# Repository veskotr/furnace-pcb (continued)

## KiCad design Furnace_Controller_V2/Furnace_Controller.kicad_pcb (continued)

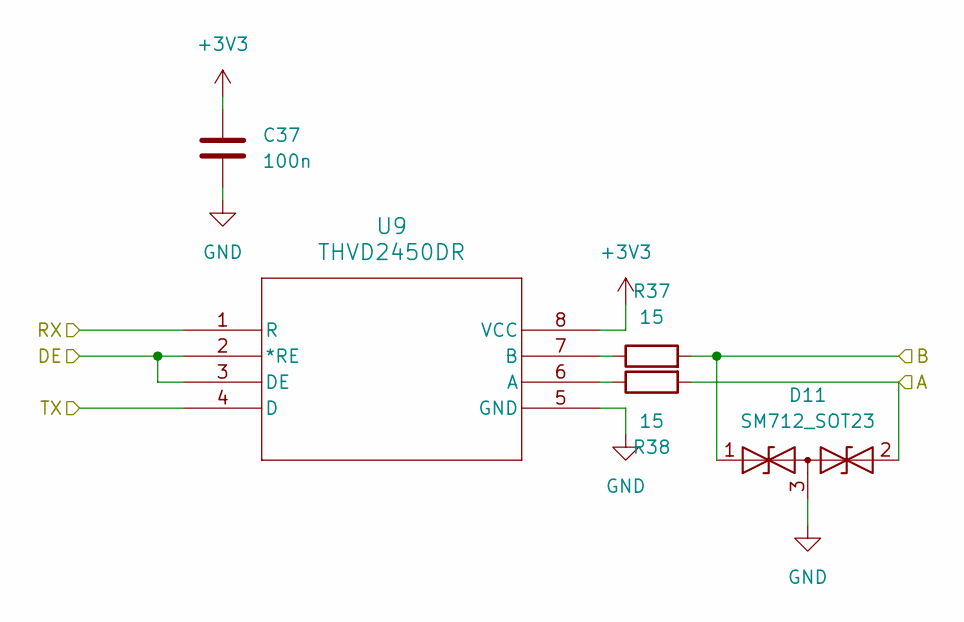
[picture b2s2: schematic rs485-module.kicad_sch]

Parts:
C37: 100n; C_0603_1608Metric
D11: SM712_SOT23; SOT-23
R37, R38: 15; R_0603_1608Metric
U9: THVD2450DR; SOIC-8_3.9x4.9mm_P1.27mm

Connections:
+3V3: C37.1, U9.8 (VCC); also elsewhere on the board
/RS_485_DIR: U9.2 (*RE), U9.3 (DE); also elsewhere on the board
/UART2_RX: U9.1 (R); also elsewhere on the board
/UART2_TX: U9.4 (D); also elsewhere on the board
/rs485-module/A: D11.2 (A2), R38.2; also elsewhere on the board
/rs485-module/B: D11.1 (A1), R37.2; also elsewhere on the board
GND: C37.2, D11.3 (common), U9.5 (GND); also elsewhere on the board
unnamed: R38.1, U9.6 (A)
unnamed: R37.1, U9.7 (B)

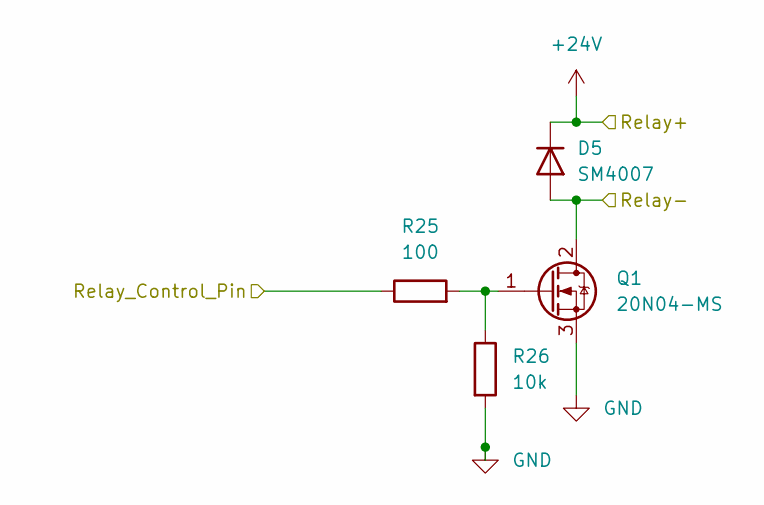
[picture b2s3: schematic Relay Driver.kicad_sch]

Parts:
D5: SM4007; D_SOD-123
Q1: 20N04-MS; Q_SOT-89
R25: 100; R_0603_1608Metric
R26: 10k; R_0603_1608Metric

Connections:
+24V: D5.1 (K); also elsewhere on the board
/Heater_Relay_Pin: R25.1; also elsewhere on the board
/Relay Driver/Relay-: D5.2 (A), Q1.2 (D); also elsewhere on the board
GND: Q1.3 (S), R26.2; also elsewhere on the board
unnamed: Q1.1 (G), R25.2, R26.1

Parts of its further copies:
D6, D7, D8: SM4007; D_SOD-123
Q2, Q3, Q4: 20N04-MS; Q_SOT-89
R27, R29, R31: 100; R_0603_1608Metric
R28, R30, R32: 10k; R_0603_1608Metric

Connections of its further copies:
+24V: D6.1 (K), D7.1 (K), D8.1 (K); also elsewhere on the board
/Aux2_Relay_Pin: R31.1; also elsewhere on the board
/Aux_Relay_Pin: R29.1; also elsewhere on the board
/Fan_Relay_Pin: R27.1; also elsewhere on the board
/Relay Driver1/Relay-: D6.2 (A), Q2.2 (D); also elsewhere on the board
/Relay Driver2/Relay-: D7.2 (A), Q3.2 (D); also elsewhere on the board
/Relay Driver3/Relay-: D8.2 (A), Q4.2 (D); also elsewhere on the board
GND: Q2.3 (S), Q3.3 (S), Q4.3 (S), R28.2, R30.2, R32.2; also elsewhere on the board
unnamed: Q2.1 (G), R27.2, R28.1
unnamed: Q3.1 (G), R29.2, R30.1
unnamed: Q4.1 (G), R31.2, R32.1

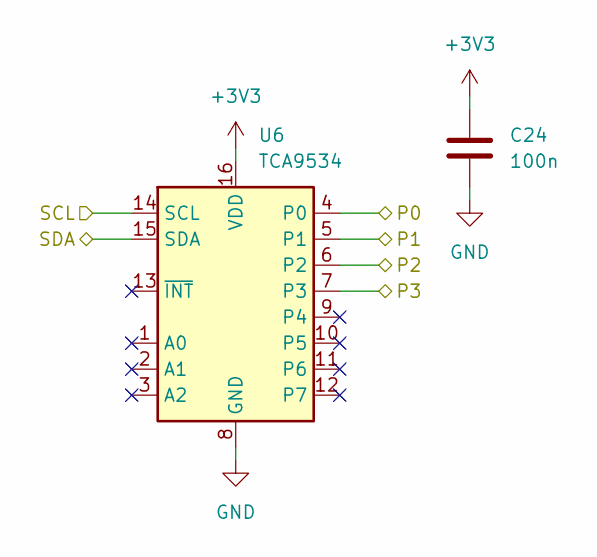
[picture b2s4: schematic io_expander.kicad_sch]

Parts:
C24: 100n; C_0603_1608Metric
U6: TCA9534; TSSOP-16_4.4x5mm_P0.65mm

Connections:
+3V3: C24.1, U6.16 (VDD); also elsewhere on the board
/Aux2_Relay_Pin: U6.7 (P3); also elsewhere on the board
/Aux_Relay_Pin: U6.6 (P2); also elsewhere on the board
/Fan_Relay_Pin: U6.5 (P1); also elsewhere on the board
/Heater_Relay_Pin: U6.4 (P0); also elsewhere on the board
/SCL: U6.14 (SCL); also elsewhere on the board
/SDA: U6.15 (SDA); also elsewhere on the board
GND: C24.2, U6.8 (GND); also elsewhere on the board

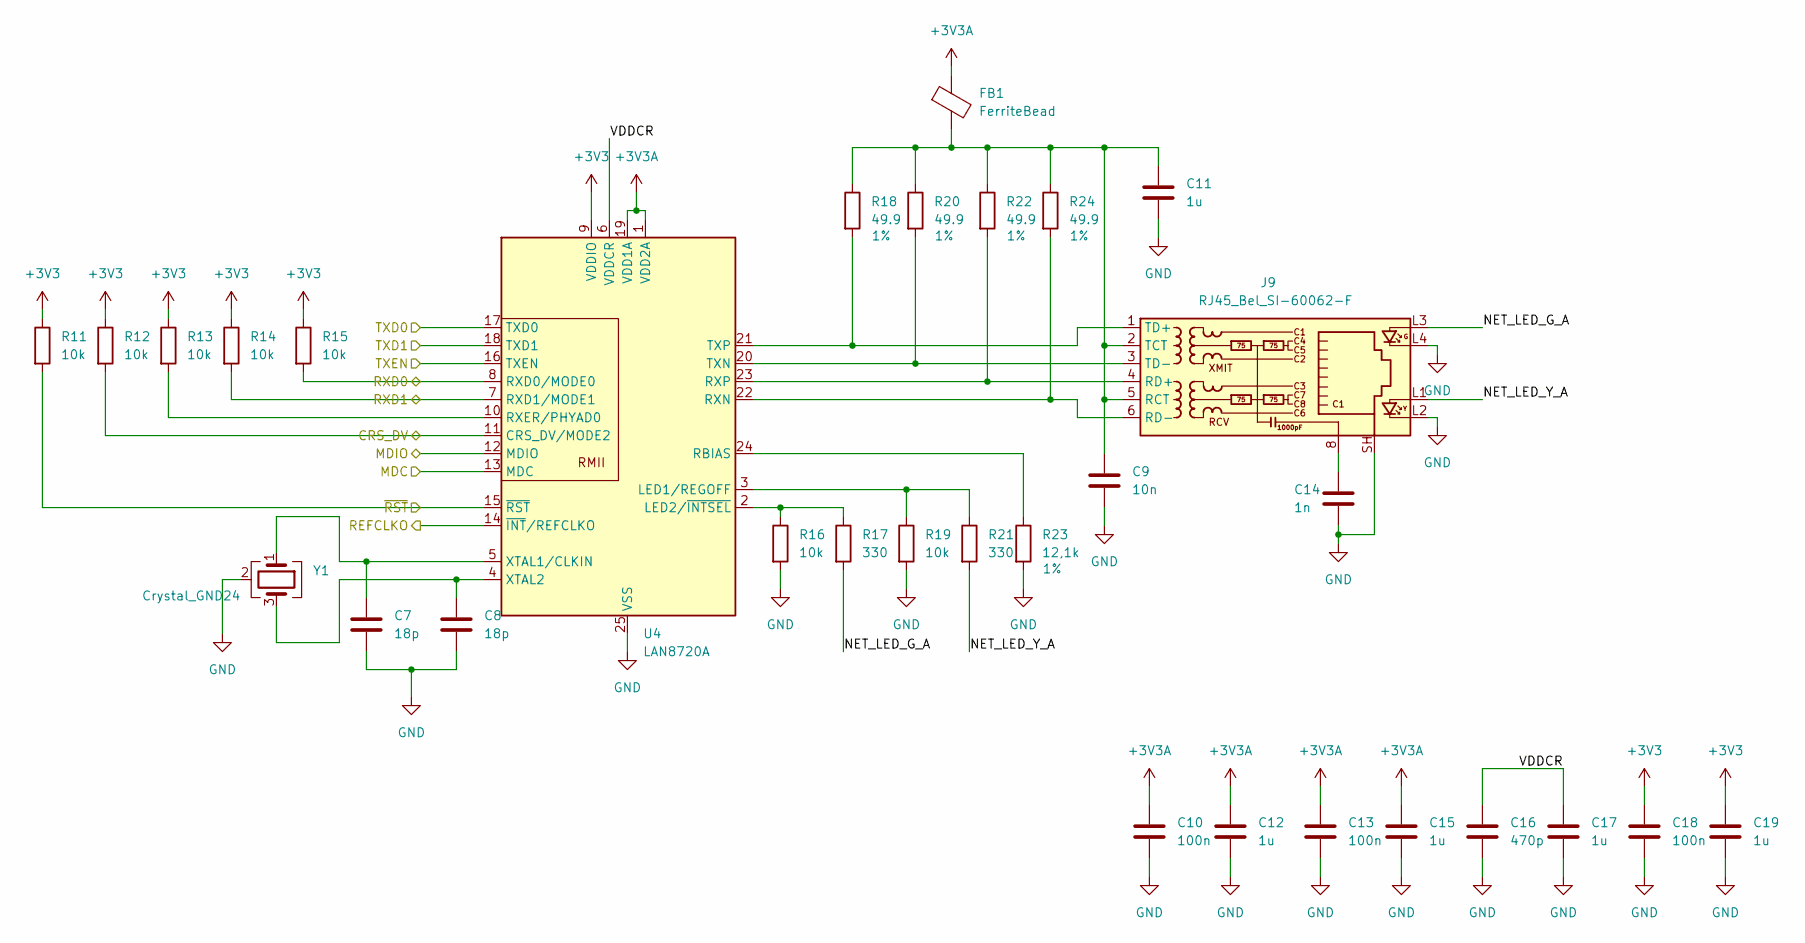
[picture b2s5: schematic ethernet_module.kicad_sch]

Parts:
C7, C8: 18p; C_0603_1608Metric
C9: 10n; C_0603_1608Metric
C10, C13, C18: 100n; C_0603_1608Metric
C11, C12, C15, C17, C19: 1u; C_0603_1608Metric
C14: 1n; C_1808_4520Metric
C16: 470p; C_0603_1608Metric
FB1: FerriteBead; L_0603_1608Metric
J9: RJ45_Bel_SI-60062-F
R11, R12, R13, R14, R15, R16, R19: 10k; R_0603_1608Metric
R17, R21: 330; R_0603_1608Metric
R18, R20, R22, R24: 49.9; R_0603_1608Metric
R23: 12,1k; R_0603_1608Metric
U4: LAN8720A; VQFN-24-1EP_4x4mm_P0.5mm_EP2.5x2.5mm_ThermalVias
Y1: Crystal_GND24; Crystal_SMD_3225-4Pin_3.2x2.5mm

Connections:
+3V3: C18.1, C19.1, R11.1, R12.1, R13.1, R14.1, R15.1, U4.9 (VDDIO); also elsewhere on the board
+3V3A: C10.1, C12.1, C13.1, C15.1, FB1.1, U4.1 (VDD2A), U4.19 (VDD1A); also elsewhere on the board
/CRS_DV: R12.2, U4.11 (CRS_DV/MODE2); also elsewhere on the board
/Ethernet Module/NET_LED_G_A: J9.L3, R17.2
/Ethernet Module/NET_LED_Y_A: J9.L1, R21.2
/Ethernet Module/VDDCR: C16.1, C17.1, U4.6 (VDDCR)
/MDC: U4.13 (MDC); also elsewhere on the board
/MDIO: U4.12 (MDIO); also elsewhere on the board
/REFCLKO: U4.14 (~INT/REFCLKO); also elsewhere on the board
/RXD0: R15.2, U4.8 (RXD0/MODE0); also elsewhere on the board
/RXD1: R14.2, U4.7 (RXD1/MODE1); also elsewhere on the board
/TXD0: U4.17 (TXD0); also elsewhere on the board
/TXD1: U4.18 (TXD1); also elsewhere on the board
/TXEN: U4.16 (TXEN); also elsewhere on the board
/~RST: R11.2, U4.15 (~RST); also elsewhere on the board
GND: C7.1, C8.2, C9.2, C10.2, C11.2, C12.2, C13.2, C14.2, C15.2, C16.2, C17.2, C18.2, C19.2, J9.L2, J9.L4, J9.SH, R16.2, R19.2, R23.2, U4.25 (VSS), Y1.2 (G), Y1.4 (G); also elsewhere on the board
unnamed: C14.1, J9.8
unnamed: C9.1, C11.1, FB1.2, J9.2 (TCT), J9.5 (RCT), R18.1, R20.1, R22.1, R24.1
unnamed: J9.4 (RD+), R22.2, U4.23 (RXP)
unnamed: J9.6 (RD-), R24.2, U4.22 (RXN)
unnamed: J9.1 (TD+), R18.2, U4.21 (TXP)
unnamed: J9.3 (TD-), R20.2, U4.20 (TXN)
unnamed: R19.1, R21.1, U4.3 (LED1/REGOFF)
unnamed: R16.1, R17.1, U4.2 (LED2/~INTSEL)
unnamed: R23.1, U4.24 (RBIAS)
unnamed: R13.2, U4.10 (RXER/PHYAD0)
unnamed: C7.2, U4.5 (XTAL1/CLKIN), Y1.1
unnamed: C8.1, U4.4 (XTAL2), Y1.3

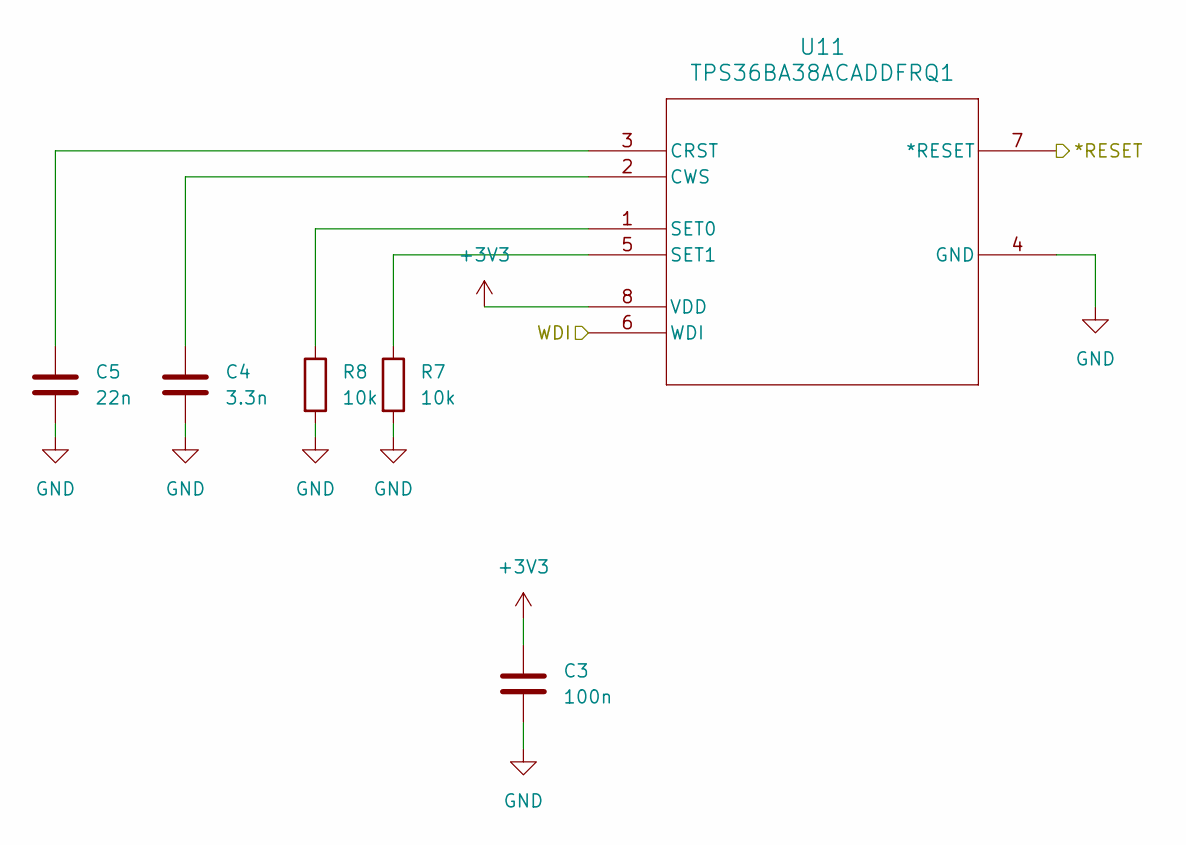
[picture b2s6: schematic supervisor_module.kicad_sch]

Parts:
C3: 100n; C_0603_1608Metric
C4: 3.3n; C_0603_1608Metric
C5: 22n; C_0603_1608Metric
R7, R8: 10k; R_0603_1608Metric
U11: TPS36BA38ACADDFRQ1; SOT-23-THIN-8_DDF_TEX

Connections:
+3V3: C3.1, U11.8 (VDD); also elsewhere on the board
/*RESET: U11.7 (*RESET); also elsewhere on the board
/WDI: U11.6 (WDI); also elsewhere on the board
GND: C3.2, C4.2, C5.2, R7.2, R8.2, U11.4 (GND); also elsewhere on the board
unnamed: C5.1, U11.3 (CRST)
unnamed: C4.1, U11.2 (CWS)
unnamed: R8.1, U11.1 (SET0)
unnamed: R7.1, U11.5 (SET1)

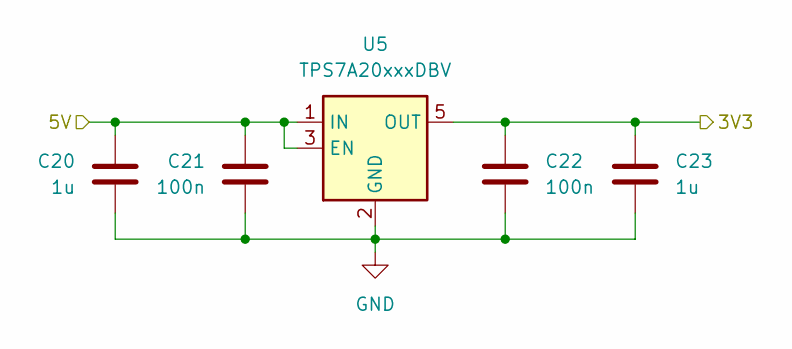
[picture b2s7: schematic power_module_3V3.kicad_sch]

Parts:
C20, C23: 1u; C_0603_1608Metric
C21, C22: 100n; C_0603_1608Metric
U5: TPS7A20xxxDBV; SOT-23-5

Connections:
+3V3A: C22.1, C23.1, U5.5 (OUT); also elsewhere on the board
+5V: C20.1, C21.1, U5.1 (IN), U5.3 (EN); also elsewhere on the board
GND: C20.2, C21.2, C22.2, C23.2, U5.2 (GND); also elsewhere on the board

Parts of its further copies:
C25, C28: 1u; C_0603_1608Metric
C26, C27: 100n; C_0603_1608Metric
U7: TPS7A20xxxDBV; SOT-23-5

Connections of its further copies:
+3V3: C27.1, C28.1, U7.5 (OUT); also elsewhere on the board
+5V: C25.1, C26.1, U7.1 (IN), U7.3 (EN); also elsewhere on the board
GND: C25.2, C26.2, C27.2, C28.2, U7.2 (GND); also elsewhere on the board

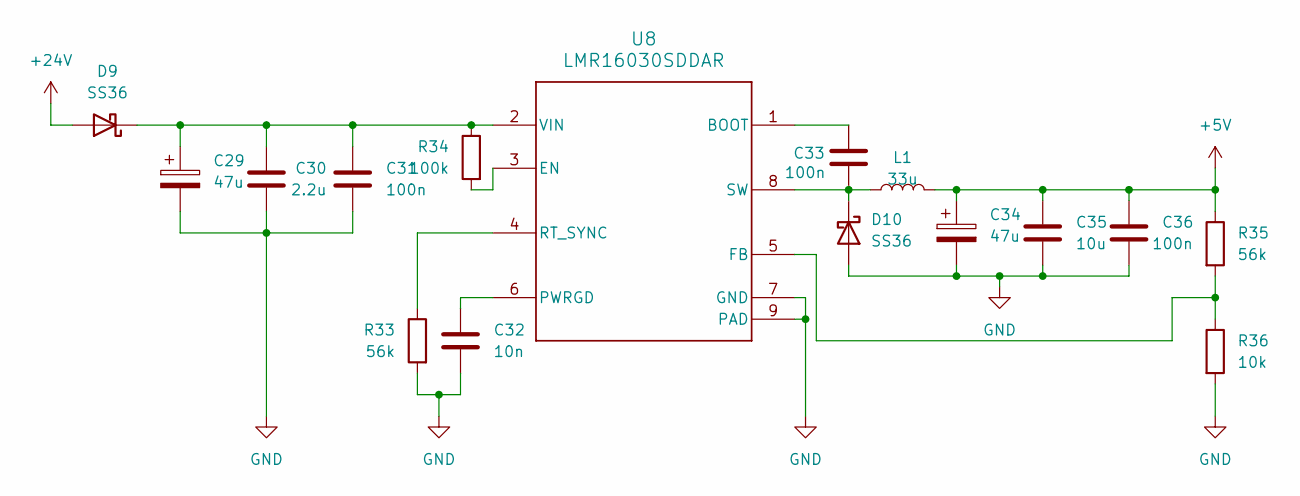
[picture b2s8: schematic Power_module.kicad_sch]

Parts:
C29, C34: 47u; CP_Radial_D6.3mm_P2.50mm
C30: 2.2u; C_0603_1608Metric
C31, C33, C36: 100n; C_0603_1608Metric
C32: 10n; C_0603_1608Metric
C35: 10u; C_0805_2012Metric
D9, D10: SS36; D_SMA
L1: 33u; L_6.3x6.3_H3
R33, R35: 56k; R_0603_1608Metric
R34: 100k; R_0603_1608Metric
R36: 10k; R_0603_1608Metric
U8: LMR16030SDDAR; SOIC-8-1EP_3.9x4.9mm_P1.27mm_EP2.29x3mm

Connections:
+5V: C34.1, C35.1, C36.1, L1.2, R35.1; also elsewhere on the board
+24V: D9.2 (A); also elsewhere on the board
GND: C29.2, C30.2, C31.2, C32.2, C34.2, C35.2, C36.2, D10.2 (A), R33.2, R36.2, U8.7 (GND), U8.9 (PAD); also elsewhere on the board
unnamed: C29.1, C30.1, C31.1, D9.1 (K), R34.1, U8.2 (VIN)
unnamed: C33.2, D10.1 (K), L1.1, U8.8 (SW)
unnamed: C33.1, U8.1 (BOOT)
unnamed: R34.2, U8.3 (EN)
unnamed: R35.2, R36.1, U8.5 (FB)
unnamed: C32.1, U8.6 (PWRGD)
unnamed: R33.1, U8.4 (RT_SYNC)

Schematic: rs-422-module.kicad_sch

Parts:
C38, C40: 100n; C_0603_1608Metric
C39, C41: 10u; C_0805_2012Metric
R41, R42, R43: 10k; R_0603_1608Metric
R44: 0; R_0603_1608Metric
U10: PTHVD2452VDR; SOIC-14_L8.7-W3.9-P1.27-LS6.0-BL

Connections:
+3V3: C38.1, C39.1, R42.1, R43.1, U10.1 (VIO); also elsewhere on the board
+5V: C40.1, C41.1, U10.14 (VCC); also elsewhere on the board
/RS-422-module/A: U10.12 (A); also elsewhere on the board
/RS-422-module/B: U10.11 (B); also elsewhere on the board
/RS-422-module/Y: U10.9 (Y); also elsewhere on the board
/RS-422-module/Z: U10.10 (Z); also elsewhere on the board
/UART1_RX: U10.2 (R); also elsewhere on the board
/UART1_TX: U10.5 (D); also elsewhere on the board
GND: C38.2, C39.2, C40.2, C41.2, R41.2, R44.2, U10.6 (GND); also elsewhere on the board
unnamed: R41.1, U10.3 (*RE)
unnamed: R42.2, U10.4 (DE)
unnamed: R43.2, R44.1, U10.8 (SLR)

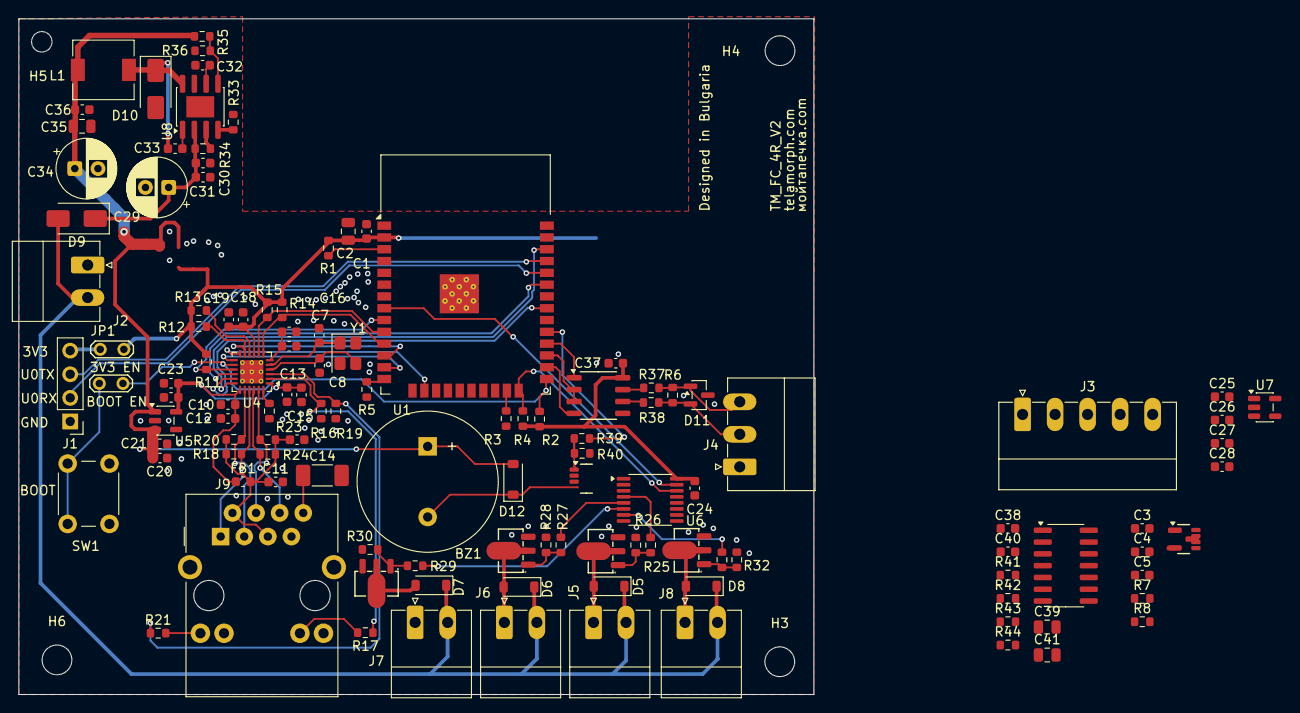
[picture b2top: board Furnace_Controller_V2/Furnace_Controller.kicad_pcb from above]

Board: 4 copper layers, 85.6 x 72.7 mm, 125 parts (0 on the bottom side), 81 nets.

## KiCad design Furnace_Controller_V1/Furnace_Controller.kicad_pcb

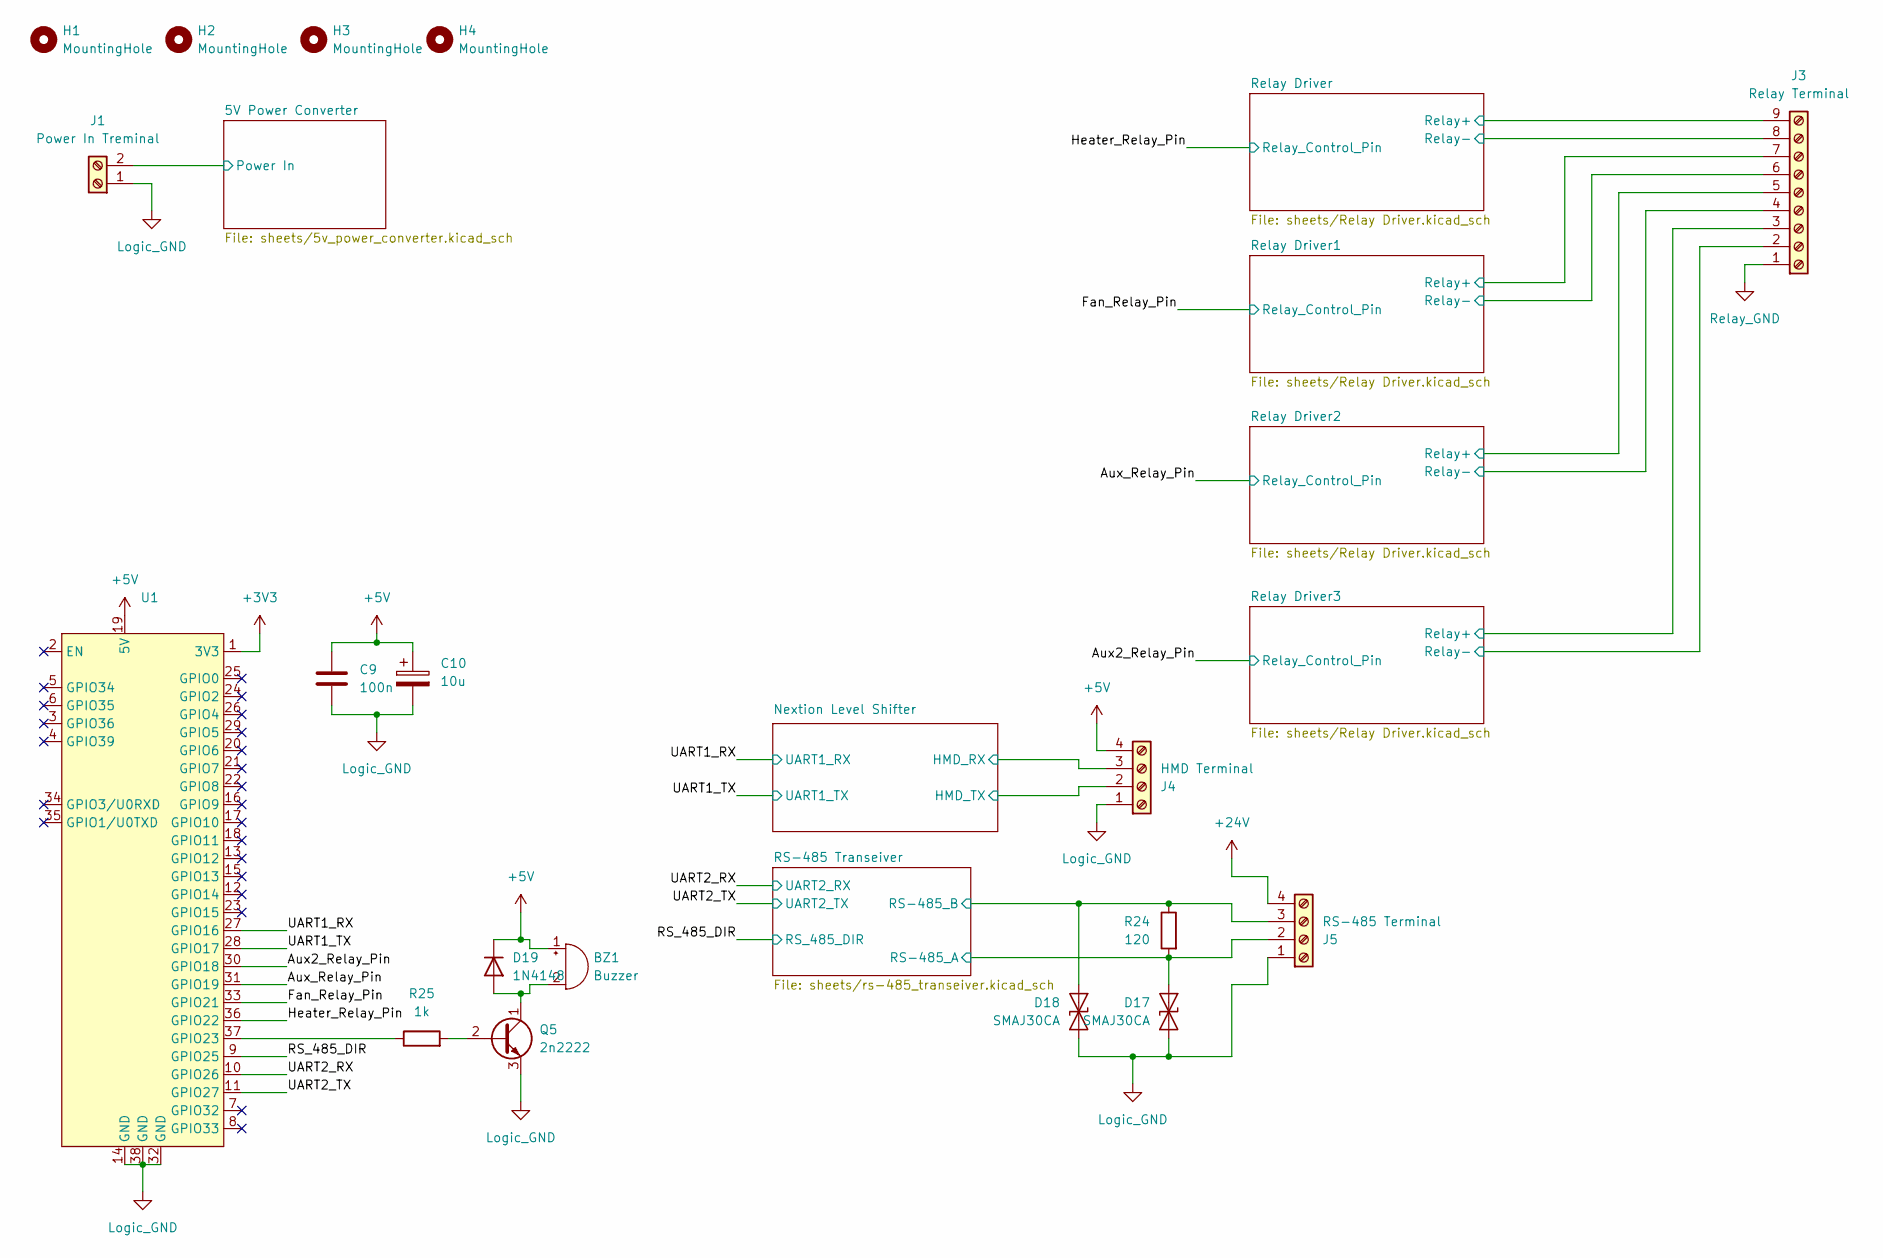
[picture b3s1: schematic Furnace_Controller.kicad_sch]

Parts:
BZ1: Buzzer; Buzzer_15x7.5RM7.6
C9: 100n; C_0805_2012Metric_Pad1.18x1.45mm_HandSolder
C10: 10u; CP_Radial_D5.0mm_P2.00mm
D17, D18: SMAJ30CA; D_SMA
D19: 1N4148; D_DO-35_SOD27_P7.62mm_Horizontal
H1, H2, H3, H4: MountingHole; MountingHole_5.3mm_M5
J1: Power In Treminal; TerminalBlock_MaiXu_MX126-5.0-02P_1x02_P5.00mm
J3: Relay Terminal; TerminalBlock_MaiXu_MX126-5.0-09P_1x09_P5.00mm
J4: HMD Terminal; TerminalBlock_MaiXu_MX126-5.0-04P_1x04_P5.00mm
J5: RS-485 Terminal; TerminalBlock_MaiXu_MX126-5.0-04P_1x04_P5.00mm
Q5: 2n2222; TO-92_Inline
R24: 120; R_0805_2012Metric_Pad1.20x1.40mm_HandSolder
R25: 1k; R_0805_2012Metric_Pad1.20x1.40mm_HandSolder
U1: ESP32_DevKitc_V4

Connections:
+3V3: U1.1 (3V3); also elsewhere on the board
+5V: BZ1.1 (+), C9.1, C10.1, D19.1 (K), J4.4, U1.19 (5V); also elsewhere on the board
+24V: J3.3, J3.5, J3.7, J3.9, J5.4; also elsewhere on the board
/Aux2_Relay_Pin: U1.30 (GPIO18); also elsewhere on the board
/Aux_Relay_Pin: U1.31 (GPIO19); also elsewhere on the board
/Fan_Relay_Pin: U1.33 (GPIO21); also elsewhere on the board
/Heater_Relay_Pin: U1.36 (GPIO22); also elsewhere on the board
/Nextion Level Shifter/HMD_RX: J4.3; also elsewhere on the board
/Nextion Level Shifter/HMD_TX: J4.2; also elsewhere on the board
/RS-485 Transeiver/RS-485_A: D17.2 (A2), J5.2, R24.2; also elsewhere on the board
/RS-485 Transeiver/RS-485_B: D18.2 (A2), J5.3, R24.1; also elsewhere on the board
/RS_485_DIR: U1.9 (GPIO25); also elsewhere on the board
/Relay Driver1/Relay-: J3.6; also elsewhere on the board
/Relay Driver2/Relay-: J3.4; also elsewhere on the board
/Relay Driver3/Relay-: J3.2; also elsewhere on the board
/UART1_RX: U1.27 (GPIO16); also elsewhere on the board
/UART1_TX: U1.28 (GPIO17); also elsewhere on the board
/UART2_RX: U1.10 (GPIO26); also elsewhere on the board
/UART2_TX: U1.11 (GPIO27); also elsewhere on the board
unnamed: BZ1.2 (-), D19.2 (A), Q5.1 (C)
unnamed: Q5.2 (B), R25.2
unnamed: R25.1, U1.37 (GPIO23)

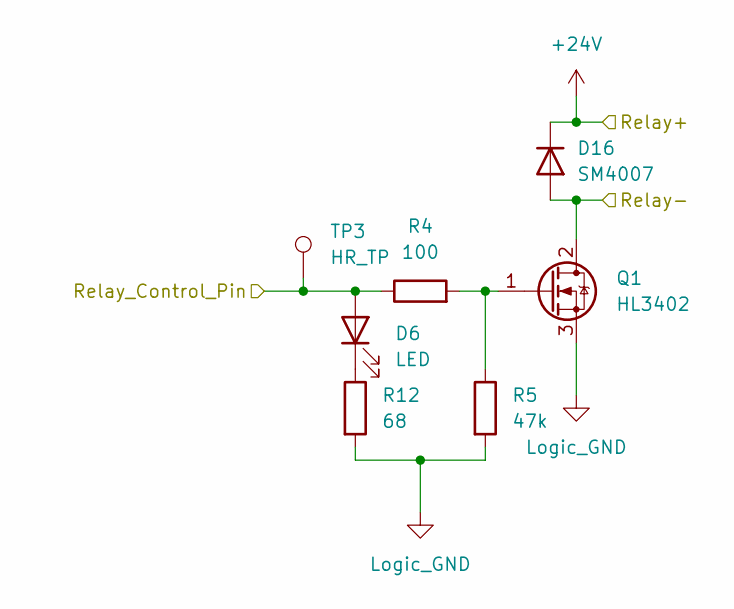
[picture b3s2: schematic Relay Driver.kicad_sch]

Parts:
D6: LED; LED_0603_1608Metric
D16: SM4007; D_SOD-123
Q1: HL3402; TSOT-23
R4: 100; R_0603_1608Metric
R5: 47k; R_0603_1608Metric
R12: 68; R_0603_1608Metric
TP3: HR_TP; TestPoint_Pad_D1.0mm

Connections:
/Heater_Relay_Pin: D6.2 (A), R4.1, TP3.1; also elsewhere on the board
unnamed: D6.1 (K), R12.1
unnamed 31: D16.1 (K); also elsewhere on the board
unnamed: Q1.1 (G), R4.2, R5.1

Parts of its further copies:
D3, D5, D8: LED; LED_0603_1608Metric
R6, R9, R13: 68; R_0603_1608Metric
R7, R10, R14: 100; R_0603_1608Metric
R8, R11, R15: 47k; R_0603_1608Metric
TP1, TP4, TP6: HR_TP; TestPoint_Pad_D1.0mm

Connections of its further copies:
/Aux2_Relay_Pin: D5.2 (A), R10.1, TP6.1; also elsewhere on the board
/Aux_Relay_Pin: D3.2 (A), R7.1, TP4.1; also elsewhere on the board
/Fan_Relay_Pin: D8.2 (A), R14.1, TP1.1; also elsewhere on the board
unnamed: D3.1 (K), R6.1
unnamed: D5.1 (K), R9.1
unnamed: D8.1 (K), R13.1
unnamed 33: R7.2, R8.1; also elsewhere on the board
unnamed 34: R10.2, R11.1; also elsewhere on the board
unnamed 35: R14.2, R15.1; also elsewhere on the board

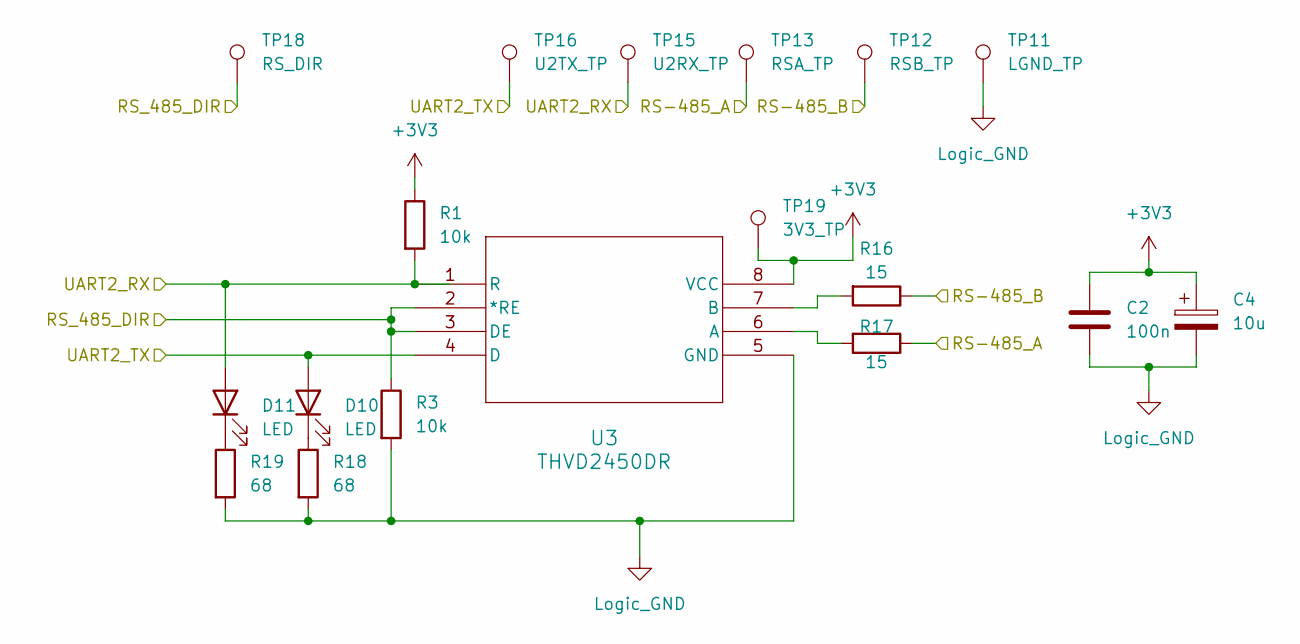
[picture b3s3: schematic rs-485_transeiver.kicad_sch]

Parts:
C2: 100n; C_0805_2012Metric_Pad1.18x1.45mm_HandSolder
C4: 10u; CP_Radial_D5.0mm_P2.00mm
D10, D11: LED; LED_0805_2012Metric
R1, R3: 10k; R_0805_2012Metric_Pad1.20x1.40mm_HandSolder
R16, R17: 15; R_0805_2012Metric_Pad1.20x1.40mm_HandSolder
R18, R19: 68; R_0805_2012Metric_Pad1.20x1.40mm_HandSolder
TP11: LGND_TP; TestPoint_Pad_D1.5mm
TP12: RSB_TP; TestPoint_Pad_D1.5mm
TP13: RSA_TP; TestPoint_Pad_D1.5mm
TP15: U2RX_TP; TestPoint_Pad_D1.5mm
TP16: U2TX_TP; TestPoint_Pad_D1.5mm
TP18: RS_DIR; TestPoint_Pad_D1.5mm
TP19: 3V3_TP; TestPoint_Pad_D1.5mm
U3: THVD2450DR; SOIC127P600X175-8N

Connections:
+3V3: C2.1, C4.1, R1.1, TP19.1, U3.8 (VCC); also elsewhere on the board
/RS-485 Transeiver/RS-485_A: R17.1, TP13.1; also elsewhere on the board
/RS-485 Transeiver/RS-485_B: R16.1, TP12.1; also elsewhere on the board
/RS_485_DIR: R3.1, TP18.1, U3.2 (*RE), U3.3 (DE); also elsewhere on the board
/UART2_RX: D11.2 (A), R1.2, TP15.1, U3.1 (R); also elsewhere on the board
/UART2_TX: D10.2 (A), TP16.1, U3.4 (D); also elsewhere on the board
unnamed: D10.1 (K), R18.1
unnamed: D11.1 (K), R19.1
unnamed: R17.2, U3.6 (A)
unnamed: R16.2, U3.7 (B)

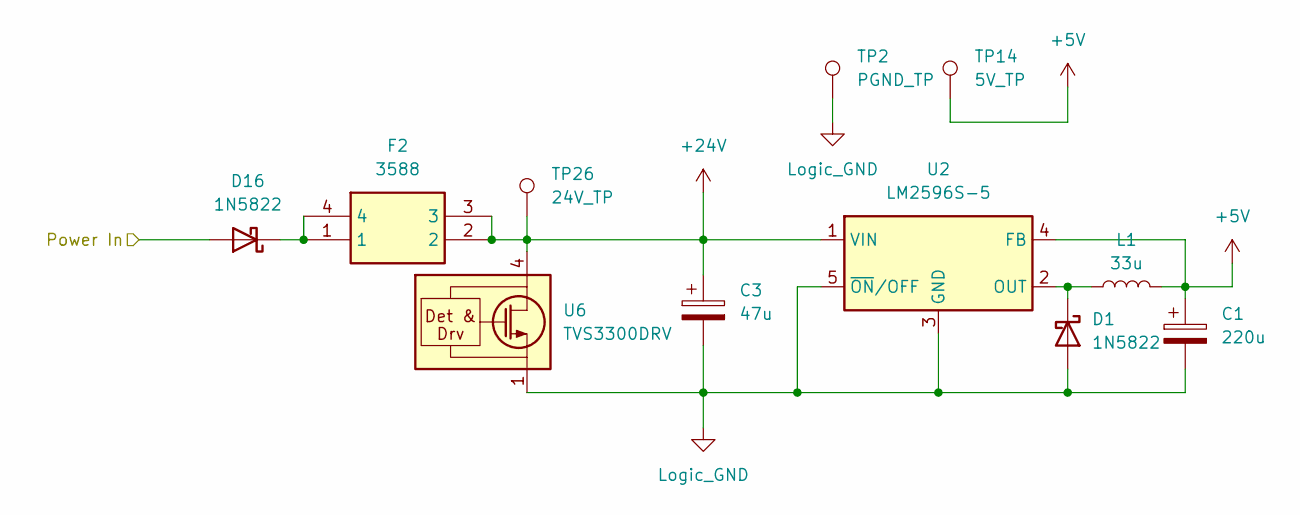
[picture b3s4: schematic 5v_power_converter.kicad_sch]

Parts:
C1: 220u; CP_Radial_D12.5mm_P5.00mm
C3: 47u; CP_Radial_D8.0mm_P2.50mm
D1, D16: 1N5822; D_DO-201AD_P15.24mm_Horizontal
F2: 3588; Mouser Part Number 534-3588
L1: 33u; SRR1260-150M
TP2: PGND_TP; TestPoint_Pad_D1.5mm
TP14: 5V_TP; TestPoint_Pad_D1.5mm
TP26: 24V_TP; TestPoint_Pad_D1.5mm
U2: LM2596S-5; TO-263-5_TabPin3
U6: TVS3300DRV; WSON-6-1EP_2x2mm_P0.65mm_EP1x1.6mm

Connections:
+5V: C1.1, L1.2, TP14.1, U2.4 (FB); also elsewhere on the board
+24V: C3.1, F2.2, F2.3, TP26.1, U2.1 (VIN), U6.4 (IN), U6.5 (IN), U6.6 (IN); also elsewhere on the board
unnamed: D1.1 (K), L1.1, U2.2 (OUT)
unnamed: D16.1 (K), F2.1, F2.4

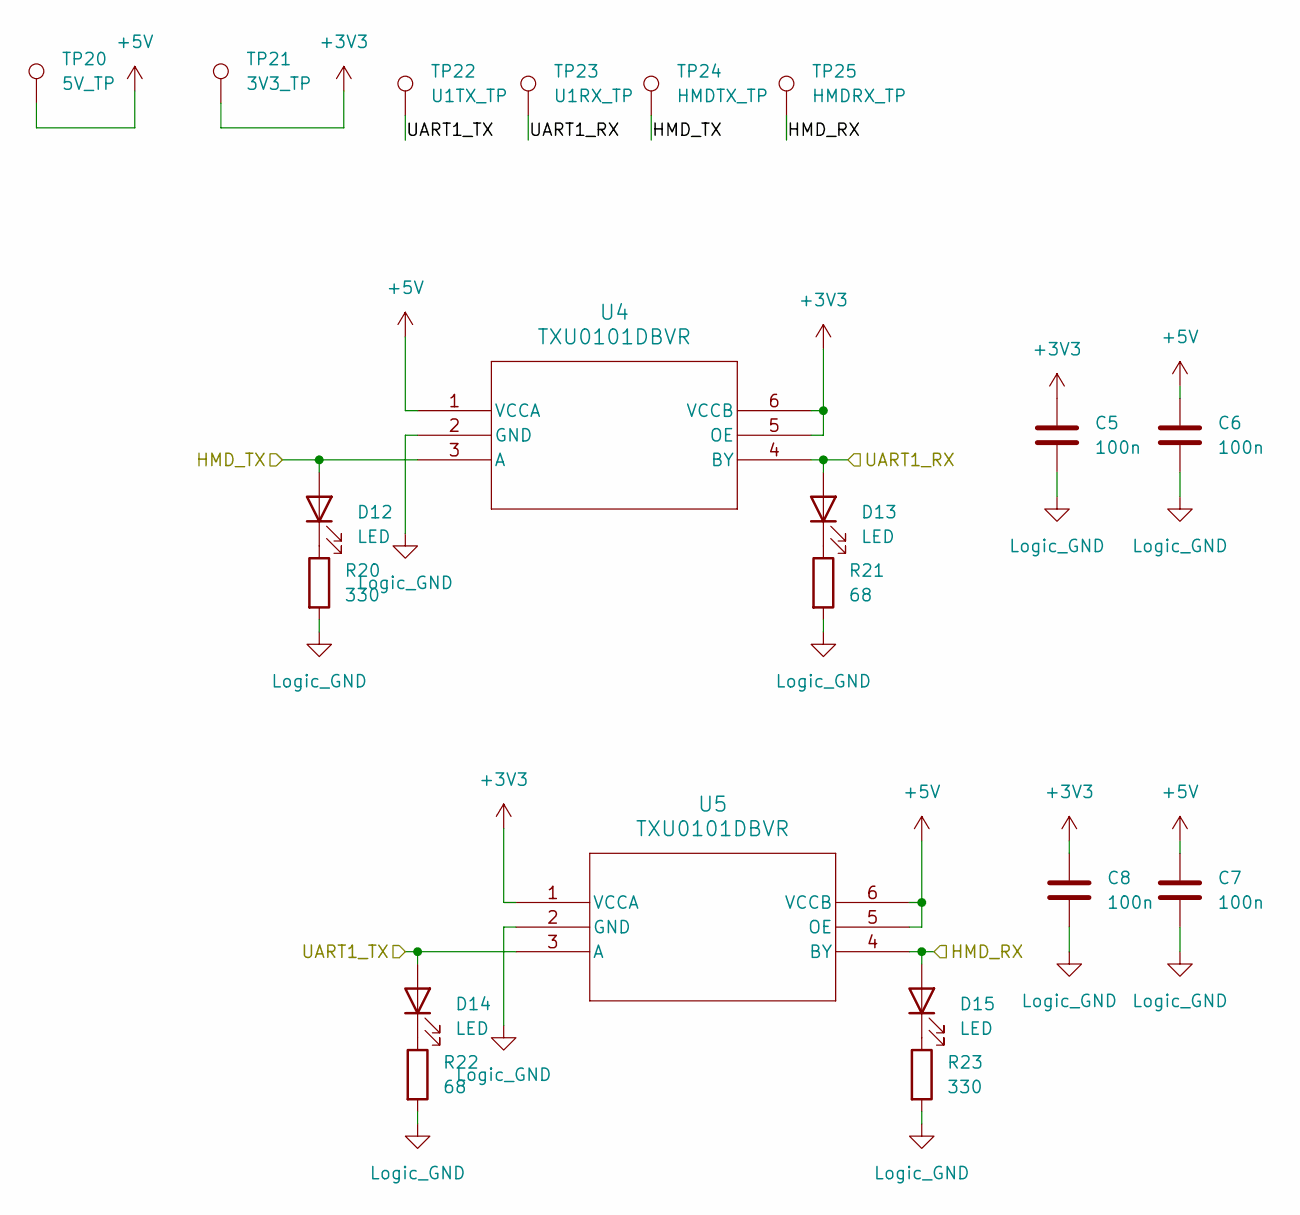
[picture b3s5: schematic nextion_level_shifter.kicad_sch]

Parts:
C5, C6, C7, C8: 100n; C_0805_2012Metric_Pad1.18x1.45mm_HandSolder
D12, D13, D14, D15: LED; LED_0805_2012Metric
R20, R23: 330; R_0805_2012Metric_Pad1.20x1.40mm_HandSolder
R21, R22: 68; R_0805_2012Metric_Pad1.20x1.40mm_HandSolder
TP20: 5V_TP; TestPoint_Pad_D1.5mm
TP21: 3V3_TP; TestPoint_Pad_D1.5mm
TP22: U1TX_TP; TestPoint_Pad_D1.5mm
TP23: U1RX_TP; TestPoint_Pad_D1.5mm
TP24: HMDTX_TP; TestPoint_Pad_D1.5mm
TP25: HMDRX_TP; TestPoint_Pad_D1.5mm
U4, U5: TXU0101DBVR; SOT95P280X145-6N

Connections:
+3V3: C5.1, C8.1, TP21.1, U4.5 (OE), U4.6 (VCCB), U5.1 (VCCA); also elsewhere on the board
+5V: C6.1, C7.1, TP20.1, U4.1 (VCCA), U5.5 (OE), U5.6 (VCCB); also elsewhere on the board
/Nextion Level Shifter/HMD_RX: D15.2 (A), TP25.1, U5.4 (BY); also elsewhere on the board
/Nextion Level Shifter/HMD_TX: D12.2 (A), TP24.1, U4.3 (A); also elsewhere on the board
/UART1_RX: D13.2 (A), TP23.1, U4.4 (BY); also elsewhere on the board
/UART1_TX: D14.2 (A), TP22.1, U5.3 (A); also elsewhere on the board
unnamed: D12.1 (K), R20.1
unnamed: D13.1 (K), R21.1
unnamed: D14.1 (K), R22.1
unnamed: D15.1 (K), R23.1

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
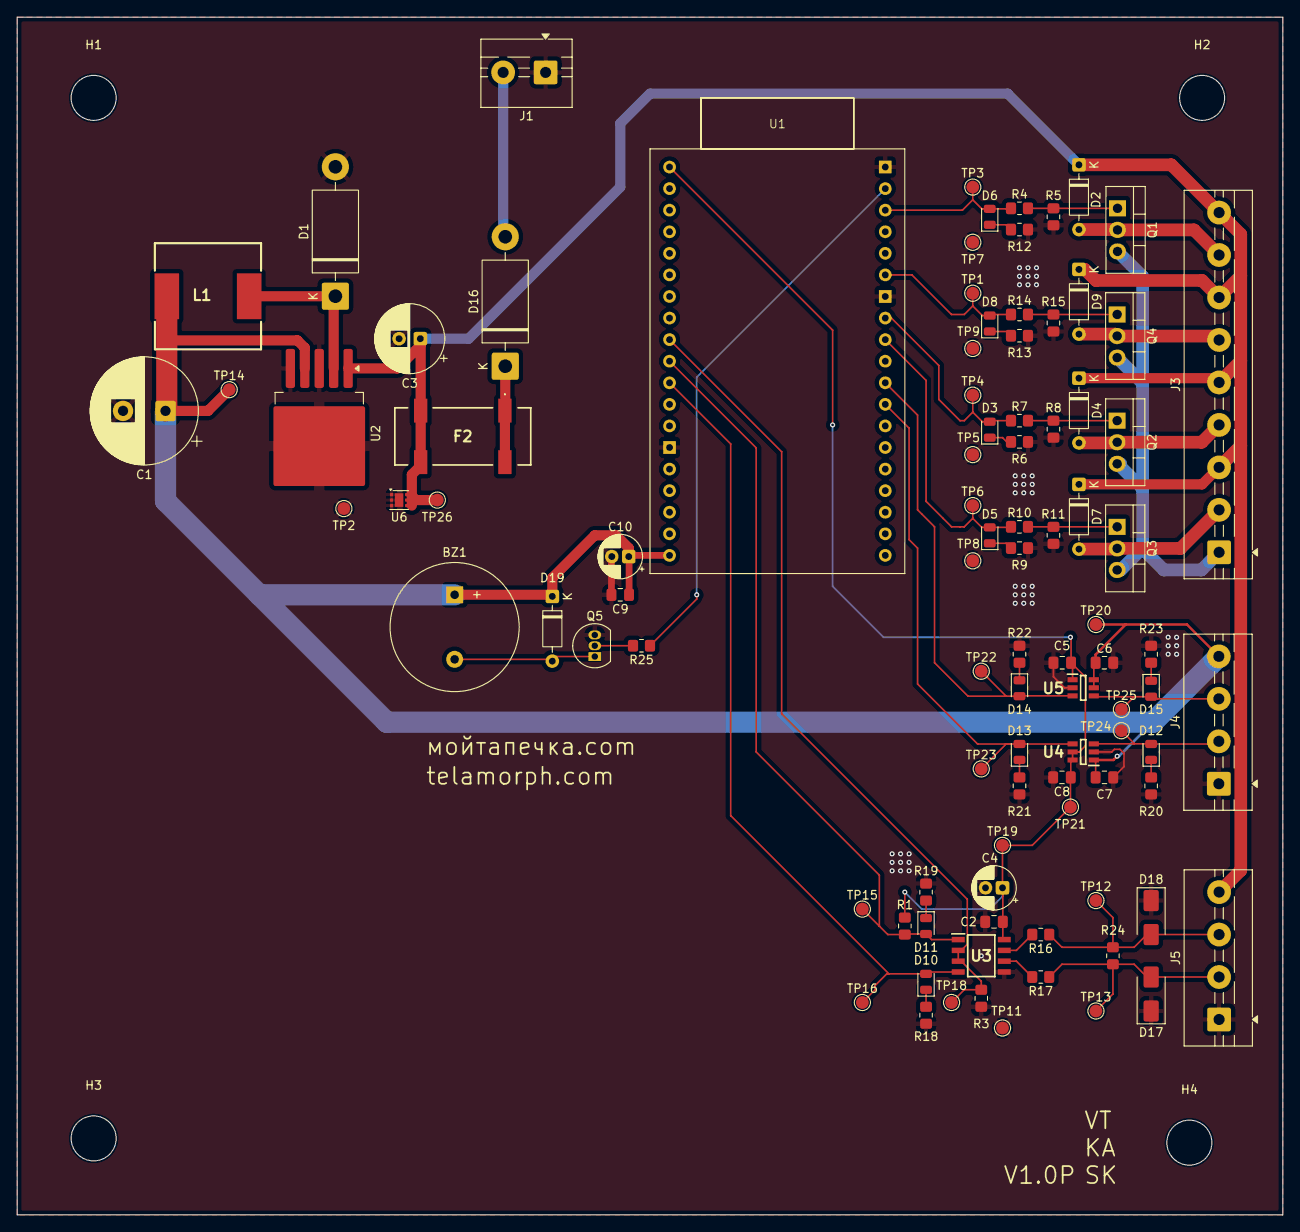
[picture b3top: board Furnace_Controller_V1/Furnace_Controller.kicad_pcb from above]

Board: 2 copper layers, 149.0 x 141.0 mm, 99 parts (0 on the bottom side), 44 nets.

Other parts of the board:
D2, D4, D7, D9: 1N4148; D_DO-35_SOD27_P7.62mm_Horizontal
Q2, Q3, Q4: IRLZ44N; TO-220-3_Vertical
TP5, TP7, TP8, TP9: LGND_TP; TestPoint_Pad_D1.5mm

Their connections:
+24V: D2.1 (K), D4.1 (K), D7.1 (K), D9.1 (K); also elsewhere on the board
/Relay Driver1/Relay-: D9.2 (A), Q4.2 (D); also elsewhere on the board
/Relay Driver2/Relay-: D4.2 (A), Q2.2 (D); also elsewhere on the board
/Relay Driver3/Relay-: D7.2 (A), Q3.2 (D); also elsewhere on the board
unnamed 33: Q2.1 (G); also elsewhere on the board
unnamed 34: Q3.1 (G); also elsewhere on the board
unnamed 35: Q4.1 (G); also elsewhere on the board

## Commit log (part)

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2026-04-04 Initial commit V1
2026-04-04 Duplicate V1 and prepare for V2 dev
2026-04-10 V2 dev
2026-06-11 Start v2
